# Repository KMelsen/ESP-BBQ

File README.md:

# ESP-BBQ
This contains all files for an ESP32 based WiFi BBQ thermometer.

* ```ESP-BBQ```: Contains the Arduino sketch with the code
* ```KiCad_PCB```: Contains all KiCad (6.0) files for the PCB
* ```Gerber_Drill_PCB.zip```: ZIP with all files needed to order the PCB
* ```PJ-210B_4-pin_2.5mm_jack.kicad_mod```: Custom KiCad footprint for the PJ-210B 4-pin 2.5mm jack

# Required parts
* **1x** PCB
* **1x** 38-pin ESP32
* **6x** PJ-210B 4-pin 2.5mm jack
* **6x** 100 Nf (104) capacitor
* **6x** 100K Ohm resistor
* **6x** 100K NTC thermistor probe
* **1x** 1.3 inch 128x64 I2C OLED display
* **2x** 19-pin 2.54mm female connector
* **1x** 4-pin 2.54mm female connector
* **8x** M3 20mm bolt
* **16x** M3 nut

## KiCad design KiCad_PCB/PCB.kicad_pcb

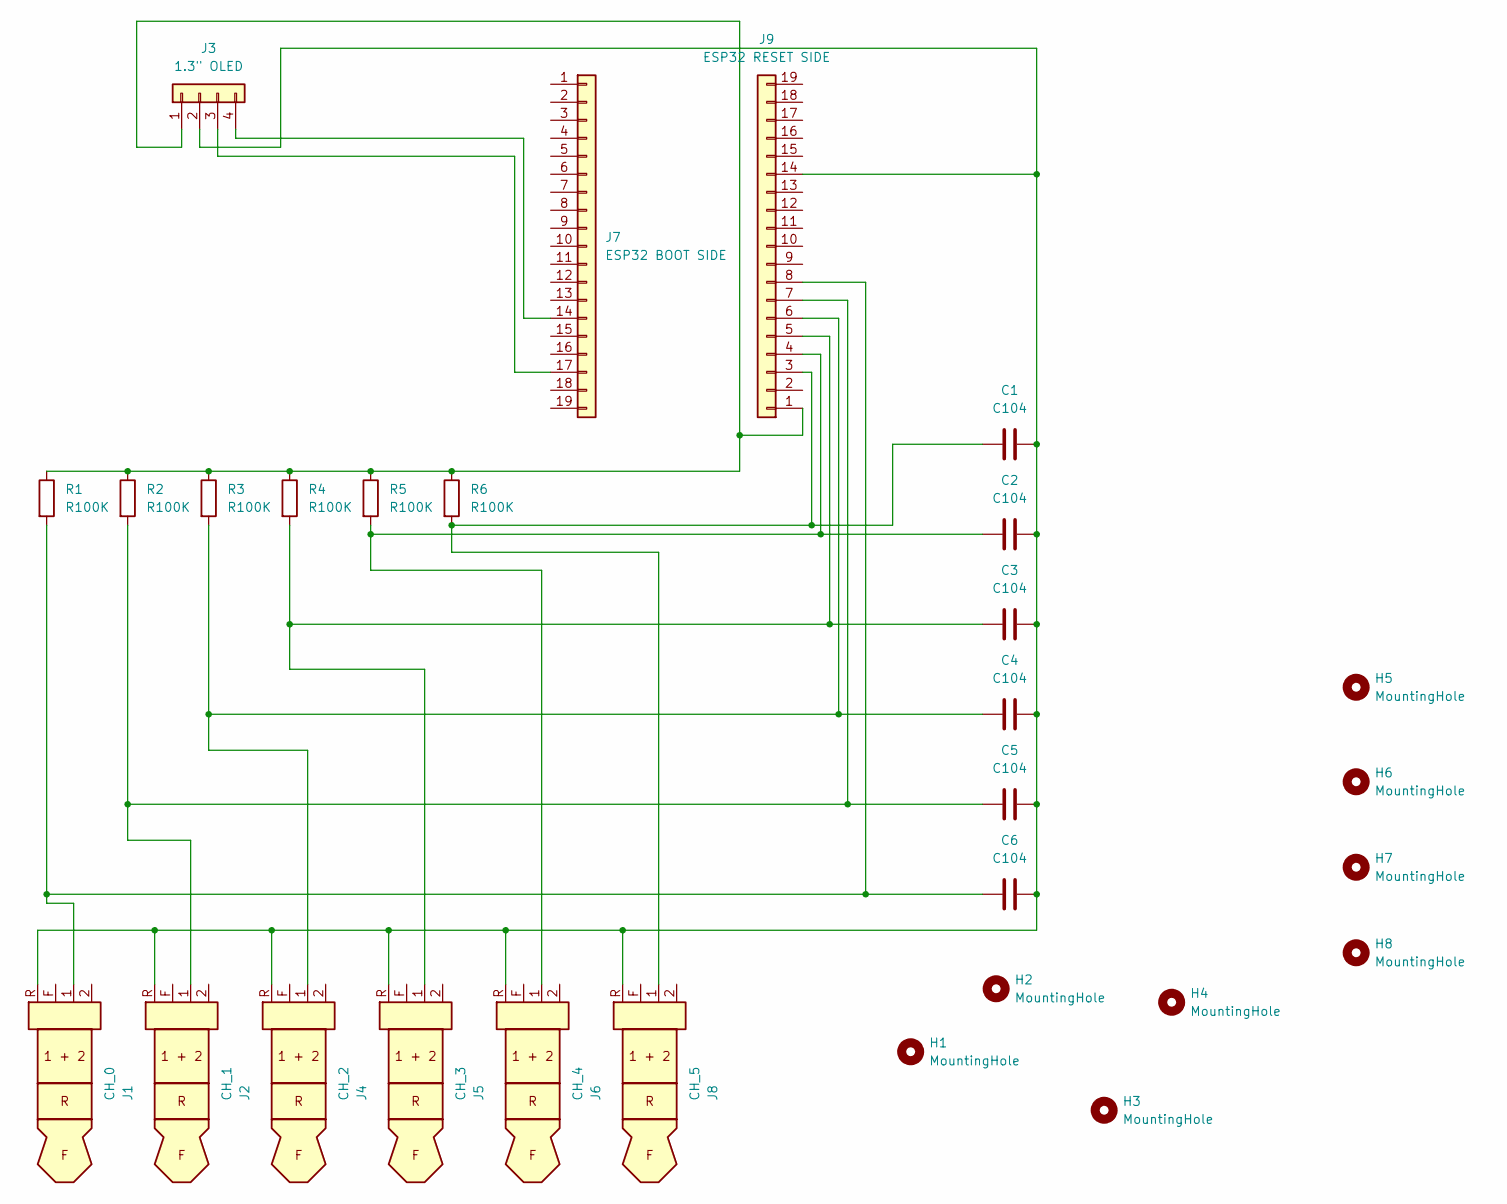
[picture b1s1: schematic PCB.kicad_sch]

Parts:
C1, C2, C3, C4, C5, C6: C104; C_Disc_D5.0mm_W2.5mm_P2.50mm
H1, H2, H3, H4, H5, H6, H7, H8: MountingHole; MountingHole_3.2mm_M3
J1: CH_0
J2: CH_1
J3: 1.3" OLED; PinSocket_1x04_P2.54mm_Vertical
J4: CH_2
J5: CH_3
J6: CH_4
J7: ESP32 BOOT SIDE; PinSocket_1x19_P2.54mm_Vertical
J8: CH_5
J9: ESP32 RESET SIDE; PinSocket_1x19_P2.54mm_Vertical
R1, R2, R3, R4, R5, R6: R100K; R_Axial_DIN0207_L6.3mm_D2.5mm_P7.62mm_Horizontal

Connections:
unnamed: C1.1, J8.1, J9.3, R6.2
unnamed: C1.2, C2.2, C3.2, C4.2, C5.2, C6.2, J1.R, J2.R, J3.2, J4.R, J5.R, J6.R, J8.R, J9.14
unnamed: C2.1, J6.1, J9.4, R5.2
unnamed: C3.1, J5.1, J9.5, R4.2
unnamed: C4.1, J4.1, J9.6, R3.2
unnamed: C5.1, J2.1, J9.7, R2.2
unnamed: C6.1, J1.1, J9.8, R1.2
unnamed: J3.1, J9.1, R1.1, R2.1, R3.1, R4.1, R5.1, R6.1
unnamed: J3.3, J7.17
unnamed: J3.4, J7.14

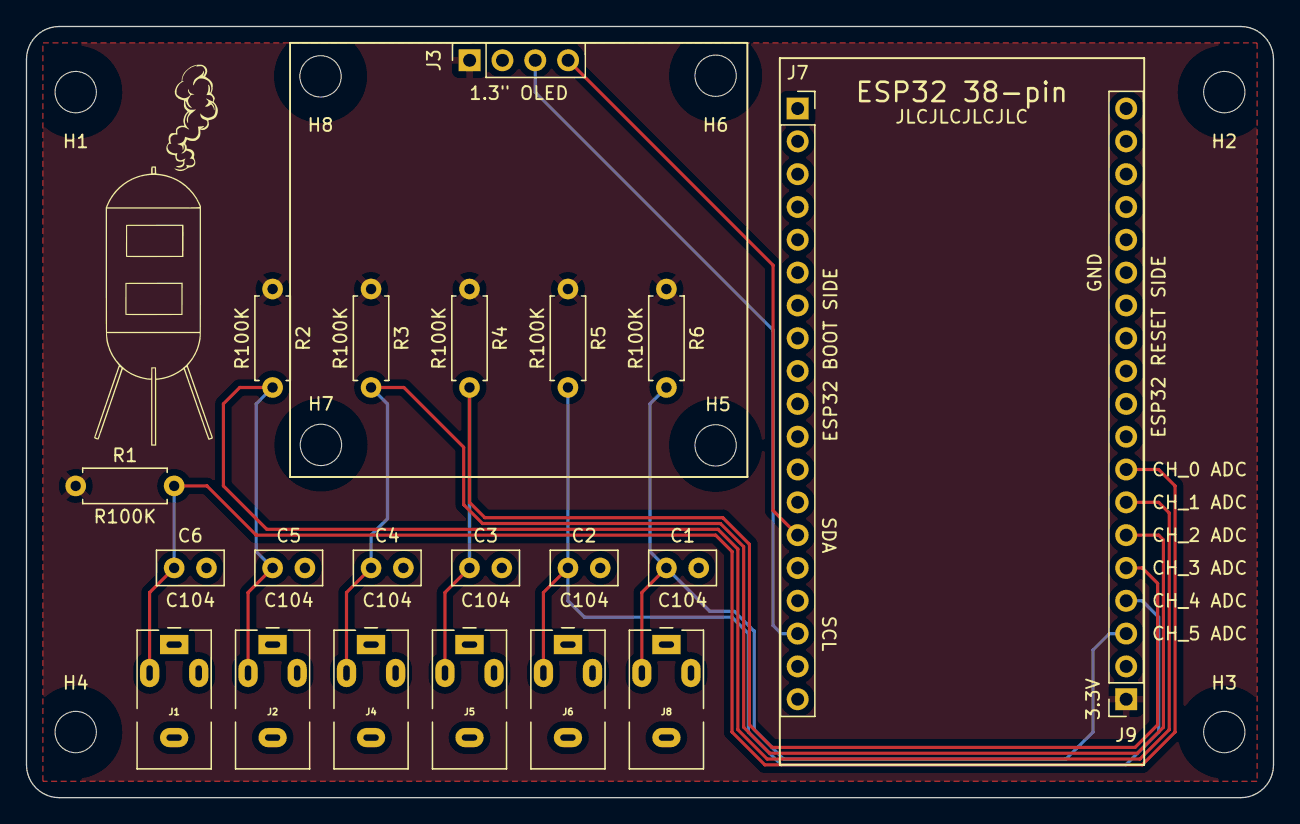
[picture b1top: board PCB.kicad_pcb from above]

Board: 2 copper layers, 96.5 x 59.7 mm, 29 parts (0 on the bottom side), 10 nets.
